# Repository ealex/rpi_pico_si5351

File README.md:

# rpi_pico_si5351
SI5351 VFO based on rpi_pico

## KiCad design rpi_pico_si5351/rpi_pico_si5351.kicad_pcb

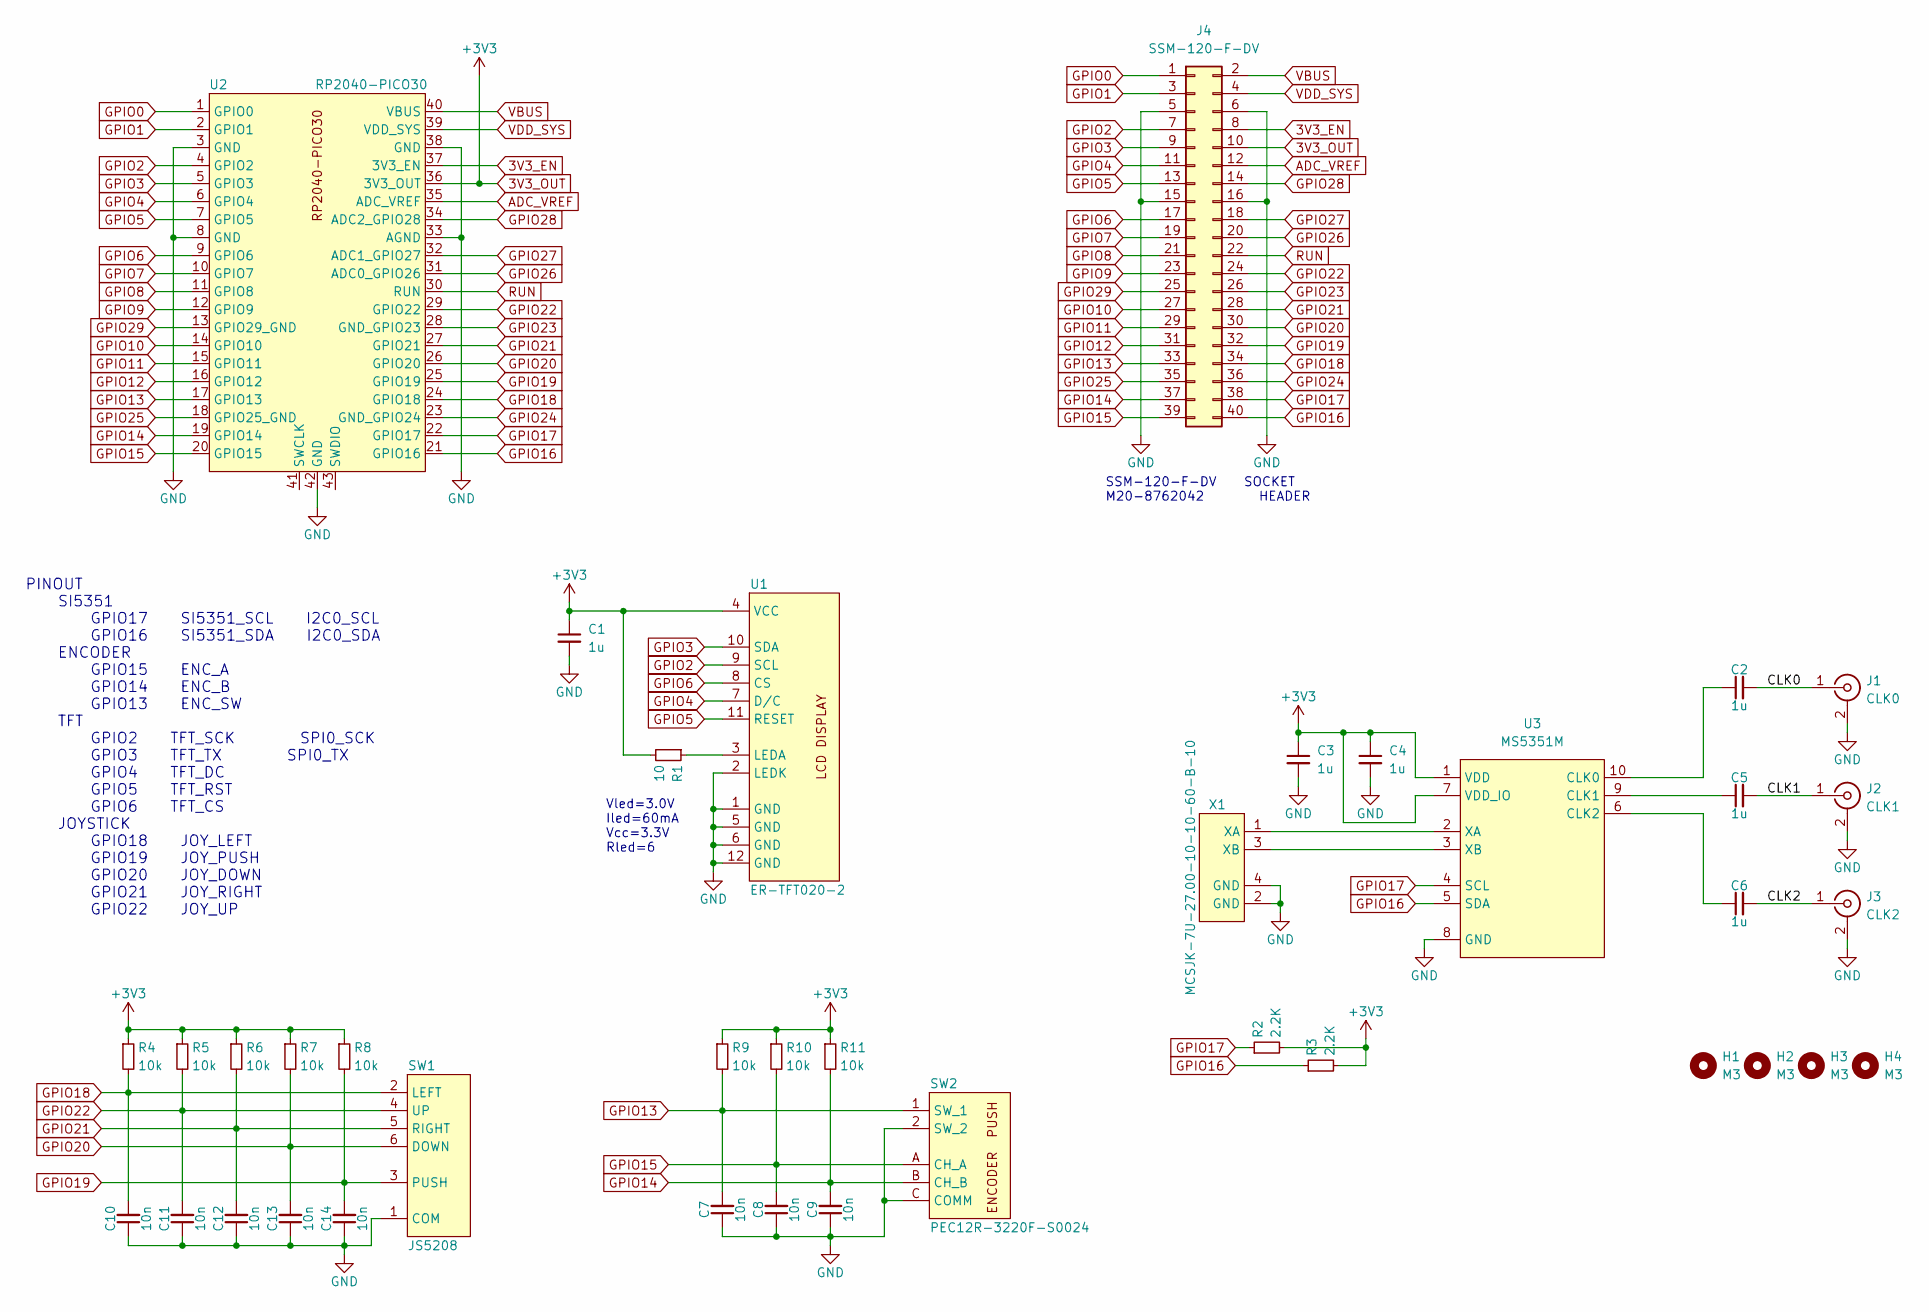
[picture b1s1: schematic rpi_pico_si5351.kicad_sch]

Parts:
C1, C2, C3, C4, C5, C6: 1u; C_0805_2012Metric
C7, C8, C9, C10, C11, C12, C13, C14: 10n; C_0805_2012Metric
H1, H2, H3, H4: M3; MountingHole_3.2mm_M3_DIN965_Pad_TopBottom
J1: CLK0; SMA
J2: CLK1; SMA
J3: CLK2; SMA
J4: SSM-120-F-DV; PinSocket_2x20_P2.54mm_Vertical_SMD
R1: 10; R_0805_2012Metric
R2, R3: 2.2K; R_0805_2012Metric
R4, R5, R6, R7, R8, R9, R10, R11: 10k; R_0805_2012Metric
SW1: JS5208; JS_5208
SW2: PEC12R-3220F-S0024
U1: ER-TFT020-2
U2: RP2040-PICO30; RP2040_PICO30_SMD
U3: MS5351M; MSOP-10_3x3mm_P0.5mm
X1: MCSJK-7U-27.00-10-10-60-B-10; Crystal_SMD_3225-4Pin_3.2x2.5mm

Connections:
3V3_EN: J4.8, U2.37 (3V3_EN)
3V3_OUT: C1.1, C3.1, C4.1, J4.10, R1.2, R2.2, R3.2, R4.1, R5.1, R6.1, R7.1, R8.1, R9.1, R10.1, R11.1, U1.4 (VCC), U2.36 (3V3_OUT), U3.1 (VDD), U3.7 (VDD_IO)
/CLK0: C2.2, J1.1 (In)
/CLK1: C5.2, J2.1 (In)
/CLK2: C6.2, J3.1 (In)
ADC_VREF: J4.12, U2.35 (ADC_VREF)
GND: C1.2, C3.2, C4.2, C7.1, C8.1, C9.1, C10.1, C11.1, C12.1, C13.1, C14.1, J1.2 (Ext), J2.2 (Ext), J3.2 (Ext), J4.5, J4.6, J4.15, J4.16, SW1.1 (COM), SW2.2 (SW_2), SW2.C (COMM), U1.1 (GND), U1.2 (LEDK), U1.5 (GND), U1.6 (GND), U1.12 (GND), U2.3 (GND), U2.8 (GND), U2.33 (AGND), U2.38 (GND), U2.42 (GND), U3.8 (GND), X1.2 (GND), X1.4 (GND)
GPIO0: J4.1, U2.1 (GPIO0)
GPIO1: J4.3, U2.2 (GPIO1)
GPIO2: J4.7, U1.9 (SCL), U2.4 (GPIO2)
GPIO3: J4.9, U1.10 (SDA), U2.5 (GPIO3)
GPIO4: J4.11, U1.7 (D/C), U2.6 (GPIO4)
GPIO5: J4.13, U1.11 (RESET), U2.7 (GPIO5)
GPIO6: J4.17, U1.8 (CS), U2.9 (GPIO6)
GPIO7: J4.19, U2.10 (GPIO7)
GPIO8: J4.21, U2.11 (GPIO8)
GPIO9: J4.23, U2.12 (GPIO9)
GPIO10: J4.27, U2.14 (GPIO10)
GPIO11: J4.29, U2.15 (GPIO11)
GPIO12: J4.31, U2.16 (GPIO12)
GPIO13: C7.2, J4.33, R9.2, SW2.1 (SW_1), U2.17 (GPIO13)
GPIO14: C9.2, J4.37, R11.2, SW2.B (CH_B), U2.19 (GPIO14)
GPIO15: C8.2, J4.39, R10.2, SW2.A (CH_A), U2.20 (GPIO15)
GPIO16: J4.40, R3.1, U2.21 (GPIO16), U3.5 (SDA)
GPIO17: J4.38, R2.1, U2.22 (GPIO17), U3.4 (SCL)
GPIO18: C10.2, J4.34, R4.2, SW1.2 (LEFT), U2.24 (GPIO18)
GPIO19: C14.2, J4.32, R8.2, SW1.3 (PUSH), U2.25 (GPIO19)
GPIO20: C13.2, J4.30, R7.2, SW1.6 (DOWN), U2.26 (GPIO20)
GPIO21: C12.2, J4.28, R6.2, SW1.5 (RIGHT), U2.27 (GPIO21)
GPIO22: C11.2, J4.24, R5.2, SW1.4 (UP), U2.29 (GPIO22)
GPIO23: J4.26, U2.28 (GND_GPIO23)
GPIO24: J4.36, U2.23 (GND_GPIO24)
GPIO25: J4.35, U2.18 (GPIO25_GND)
GPIO26: J4.20, U2.31 (ADC0_GPIO26)
GPIO27: J4.18, U2.32 (ADC1_GPIO27)
GPIO28: J4.14, U2.34 (ADC2_GPIO28)
GPIO29: J4.25, U2.13 (GPIO29_GND)
unnamed: C2.1, U3.10 (CLK0)
unnamed: C5.1, U3.9 (CLK1)
unnamed: C6.1, U3.6 (CLK2)
unnamed: R1.1, U1.3 (LEDA)
unnamed: U3.2 (XA), X1.1 (XA)
unnamed: U3.3 (XB), X1.3 (XB)
RUN: J4.22, U2.30 (RUN)
VBUS: J4.2, U2.40 (VBUS)
VDD_SYS: J4.4, U2.39 (VDD_SYS)

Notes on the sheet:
SSM-120-F-DV SOCKET M20-8762042 HEADER
Vled=3.0V Iled=60mA Vcc=3.3V Rled=6
PINOUT SI5351 GPIO17 SI5351_SCL I2C0_SCL GPIO16 SI5351_SDA I2C0_SDA ENCODER GPIO15 ENC_A GPIO14 ENC_B GPIO13 ENC_SW TFT GPIO2 TFT_SCK SPI0_SCK GPIO3 TFT_TX SPI0_TX GPIO4 TFT_DC GPIO5 TFT_RST GPIO6 TFT_CS JOYSTICK GPIO18 JOY_LEFT GPIO19 JOY_PUSH GPIO20 JOY_DOWN GPIO21 JOY_RIGHT GPIO22 JOY_UP

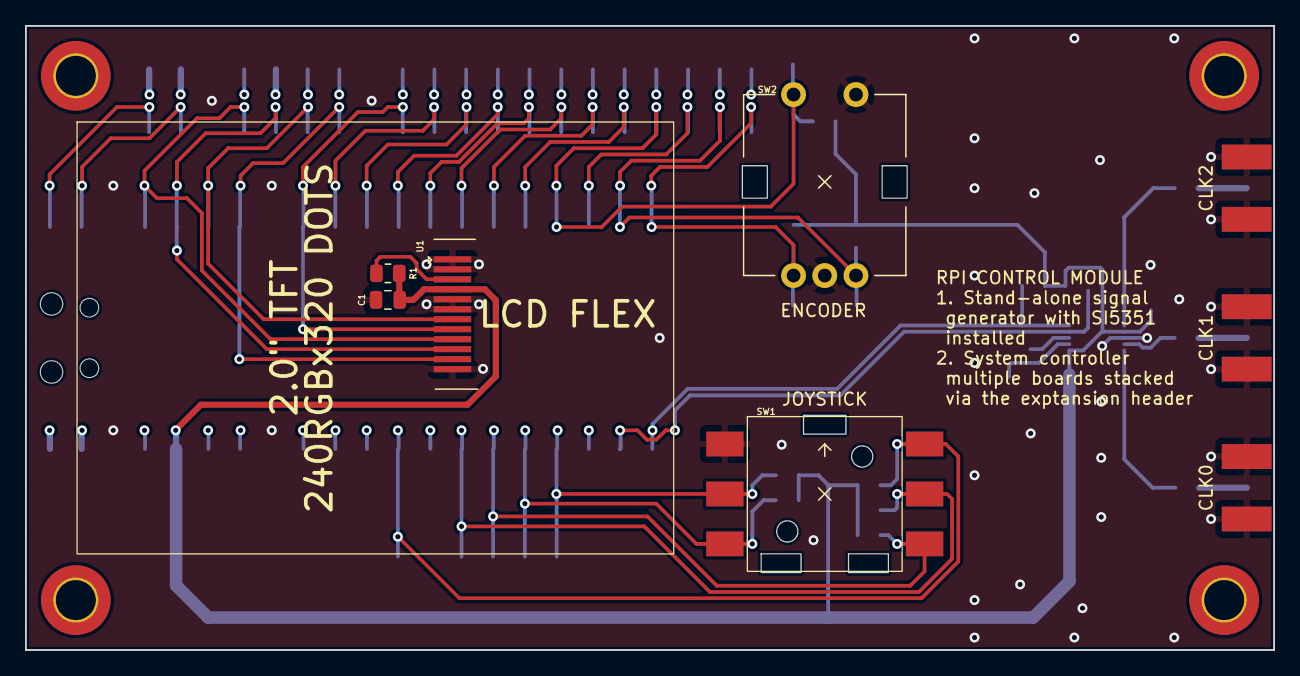
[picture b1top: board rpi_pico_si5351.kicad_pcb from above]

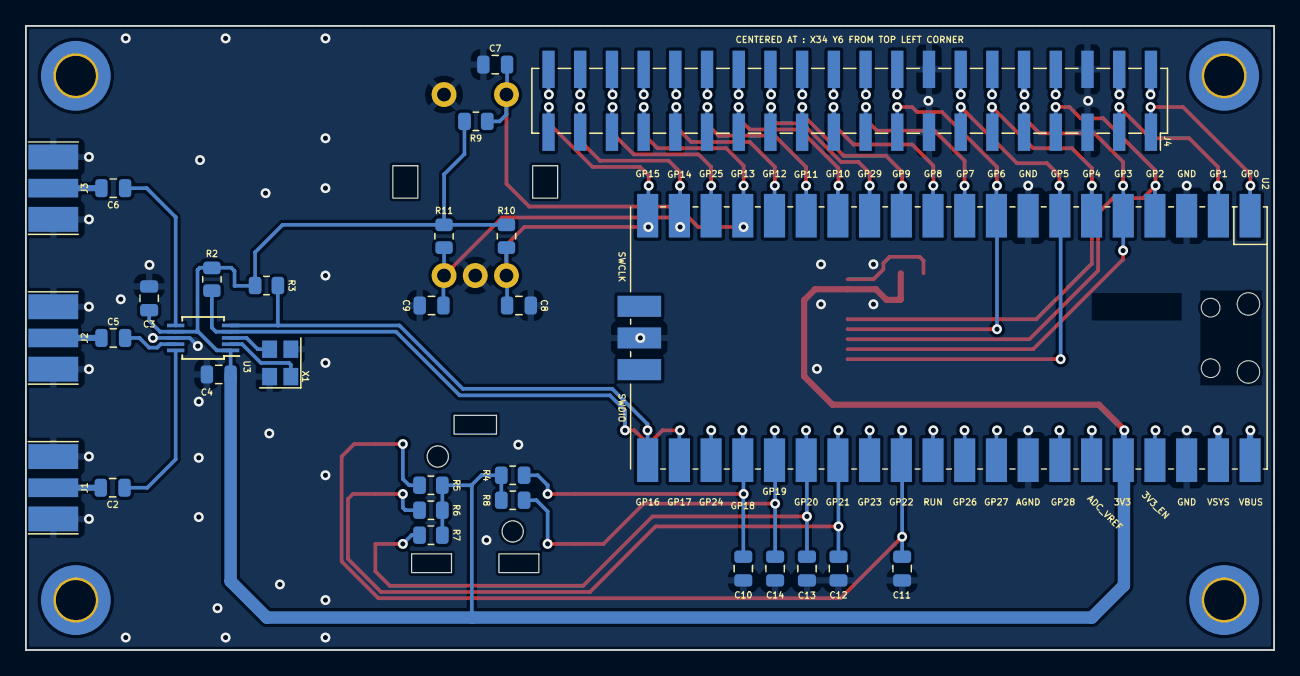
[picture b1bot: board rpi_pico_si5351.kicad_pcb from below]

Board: 4 copper layers, 100.0 x 50.0 mm, 39 parts (30 on the bottom side), 46 nets.

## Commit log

2023-12-07 add datasheets for chosen parts
2023-12-07 add synth and crystal
2023-12-07 schematic, initial
2023-12-08 schematic and parts update
2023-12-15 add LCD datasheet
2023-12-15 add new parts and 3d models
2023-12-15 initial board layout
2023-12-19 add board render
2023-12-19 update renders
2023-12-19 fix footprints, update schematic
2024-02-14 add multi-board header to allow stacking of multiple modules
2024-02-15 clean-up, add STACk connector
2024-02-19 production data
